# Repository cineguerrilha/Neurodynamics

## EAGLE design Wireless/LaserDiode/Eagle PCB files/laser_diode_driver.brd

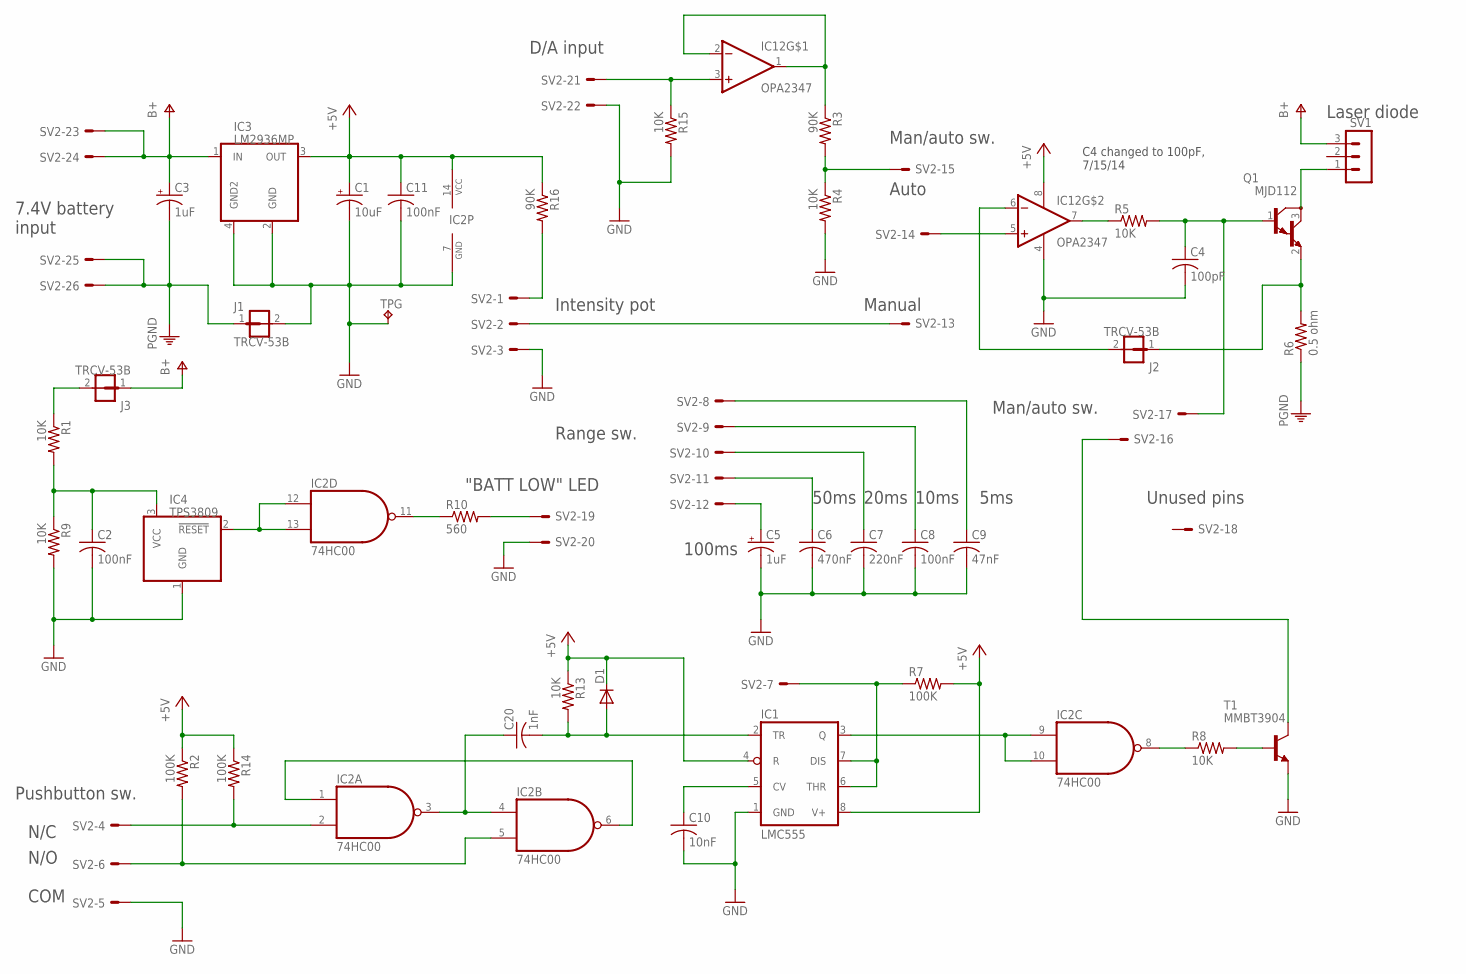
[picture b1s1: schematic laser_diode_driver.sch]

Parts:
C1: 10uF; SMC_B
C2, C8, C11: 100nF; C0805
C3, C5: 1uF; SMC_B
C4: 100pF; C0805
C6: 470nF; C0805
C7: 220nF; C0805
C9: 47nF; C0805
C10: 10nF; C0805
C20: 1nF; C0805
D1: DIODE-SOD123; SOD123
IC1: LMC555; SO08
IC2: 74HC00; SO14
IC3: LM2936MP; SOT223
IC4: TPS3809; SOT23
IC12: OPA2347; SO08
J1, J2, J3: TRCV-53B; JUMPER-TRACE-CONVERT-53-VER2
Q1: MJD112; TO252
R1, R4, R5, R8, R9, R13, R15: 10K; R0805
R2, R7, R14: 100K; R0805
R3, R16: 90K; R0805
R6: 0.5 ohm; R2512
R10: 560; R0805
SV1: MA03-1
SV2: ML26LE; ML26L
T1: MMBT3904; SOT23-BEC
TPG: TP-040-100; P1-040-100

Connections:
+5V: C1.+, C11.1, D1.C, IC1.4 (R), IC1.8 (V+), IC2.14 (VCC), IC3.3 (OUT), IC12.8 (PWR+), R2.1, R7.2, R13.1, R14.1, R16.1
B+: C3.+, IC3.1 (IN), J3.1, SV1.3, SV2.23, SV2.24
GND: C1.-, C2.2, C4.2, C5.-, C6.2, C7.2, C8.2, C9.2, C10.2, C11.2, IC1.1 (GND), IC2.7 (GND), IC3.2 (GND), IC3.4 (GND2), IC4.1 (GND), IC12.4 (PWR-), J1.2, R4.2, R9.2, R15.2, SV2.3, SV2.5, SV2.20, SV2.22, T1.E, TPG.P$1
unnamed: C20.1, IC2.3 (O), IC2.4 (I0)
unnamed: IC12.5 (+IN), SV2.14
unnamed: IC2.1 (I0), IC2.6 (O)
unnamed: IC2.2 (I1), R14.2, SV2.4
unnamed: IC2.5 (I1), R2.2, SV2.6
unnamed: C20.2, D1.A, IC1.2 (TR), R13.2
unnamed: C5.+, SV2.12
unnamed: IC12.7 (OUT), R5.1
unnamed: C4.1, Q1.1 (B), R5.2, SV2.17
unnamed: R16.2, SV2.1
unnamed: IC12.3 (+IN), R15.1, SV2.21
unnamed: IC12.1 (OUT), IC12.2 (-IN), R3.1
unnamed: R3.2, R4.1, SV2.15
unnamed: SV2.2, SV2.13
unnamed: Q1.3 (C), SV1.1
unnamed: IC12.6 (-IN), J2.2
unnamed: C6.1, SV2.11
unnamed: C7.1, SV2.10
unnamed: C8.1, SV2.9
unnamed: C9.1, SV2.8
unnamed: IC1.6 (THR), IC1.7 (DIS), R7.1, SV2.7
unnamed: C10.1, IC1.5 (CV)
unnamed: IC1.3 (Q), IC2.9 (I0), IC2.10 (I1)
unnamed: IC2.8 (O), R8.1
unnamed: R8.2, T1.B
unnamed: SV2.16, T1.C
unnamed: C2.1, IC4.3 (VCC), R1.2, R9.1
unnamed: J2.1, Q1.2 (E), R6.2
unnamed: IC2.12 (I0), IC2.13 (I1), IC4.2 (!RESET)
unnamed: IC2.11 (O), R10.1
unnamed: R10.2, SV2.19
unnamed: J3.2, R1.1
PGND: C3.-, J1.1, R6.1, SV2.25, SV2.26

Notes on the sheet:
Intensity pot
Man/auto sw.
Pushbutton sw.
D/A input
N/C
N/O
"BATT LOW" LED
Range sw.
Auto
Manual
7.4V battery input
Unused pins
Laser diode
COM
5ms
10ms
20ms
50ms
100ms
C4 changed to 100pF, 7/15/14

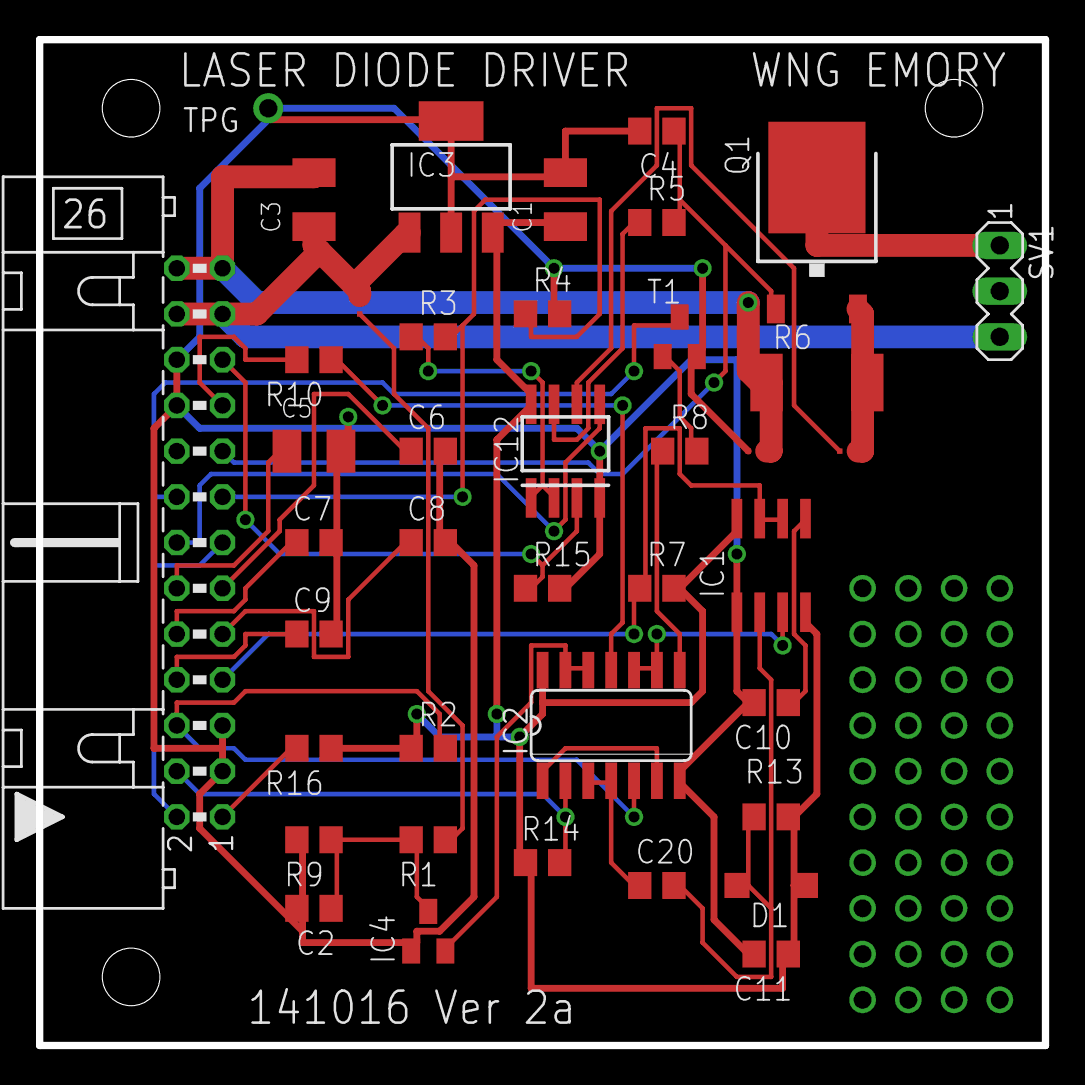
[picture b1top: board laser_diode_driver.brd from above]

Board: 4 copper layers, 55.9 x 55.9 mm, 40 parts (0 on the bottom side), 36 nets.

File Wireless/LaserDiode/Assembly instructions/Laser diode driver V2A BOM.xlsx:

Quan. | Value | Eagle Device | Part names | Digikey p/n | Notes
PC Board Parts - vendor: Digikey (www.digikey.com)
1.0 | 0.5 ohm | R-US_R2512 | R6 | CSRN2512FKR500CT-ND
1.0 | 560 | R-US_R0805 | R10 | 311-560CRCT-ND
7.0 | 10K | R-US_R0805 | R1 R4 R5 R8 R9 R13 R15 | 311-10.0KCRCT-ND
2.0 | 90.9K | R-US_R0805 | R3 R16 | 311-90.9KCRCT-ND
3.0 | 100K | R-US_R0805 | R2 R7 R14 | 311-100KCRCT-ND
1.0 | 100pF | C-USC0805 | C4 | 399-7981-1-ND
1.0 | 1nF | C-USC0805 | C20 | 399-1147-1-ND
1.0 | 10nF | C-USC0805 | C10 | 399-1158-1-ND
1.0 | 47nF | C-USC0805 | C9 | 399-1166-1-ND
3.0 | 100nF | C-USC0805 | C2 C8 C11 | 399-1170-1-ND
1.0 | 220nF | C-USC0805 | C7 | 399-3491-1-ND
1.0 | 470nF | C-USC0805 | C6 | 399-8098-1-ND
2.0 | 1uF | CPOL-USSMCB | C3 C5 | 399-3680-1-ND | polarized
1.0 | 10uF | CPOL-USSMCB | C1 | 399-8269-1-ND | polarized
1.0 | LM2936MP | LM2936MP | IC3 | 296-37374-1-ND | voltage regulator
1.0 | LMC555 | LM555D | IC1 | LMC555CMX/NOPBCT-ND | timer
1.0 | MJD112 | MJD112 | Q1 | 497-2462-1-ND | darlington transistor
1.0 | MMBT3904 | MMBT3904LT1 | T1 | MMBT3904LT1GOSCT-ND | NPN transistor
1.0 | 74HC00 | 74ALS00D | IC2 | 568-1379-1-ND | NAND gate
1.0 | OPA2347 | OPA2227-SO8 | IC12 | OPA2347UACT-ND | op amp
1.0 | TP-040-100 | TP-040-100 | TPG | 5001K-nd | test point
1.0 | TPS3809K33 | TPS3809 | IC4 | 296-15644-1-NS | low-battery warning
1.0 |  | DIODE-SOD123 | D1 | 1N4148WTPMSCT-ND | diode
1.0 |  | MA03-1 | SV1 | A19470-ND | 3-pin connector
1.0 |  |  |  | A99614-ND | mate for MA03
3.0 |  |  |  | A99620 | pins for MA03
1.0 |  | ML26LE | SV2 | A97488-ND | 26-pin IDC connector
1.0 |  |  |  | CKC26G | IDC socket for above
1.0 |  |  |  | MC26M-5-ND | 26-cond. ribbon cable
Off-board parts
1.0 |  |  | S1 | CKN1649-ND, CKN1210-ND | pushbutton and cap
1.0 |  |  | S2 | GH5604-ND | range switch
1.0 |  |  | S3 | CKN1034-ND | manual/auto switch
1.0 |  |  | S4 | 450-1523-ND | power switch
1.0 |  |  | J1 | CP-6-ND | charging jack
1.0 |  |  | P1 | CP3-1001-ND | charging plug
1.0 | 10K |  | VR1 | 95A1A-B24-A15L-ND | intensity pot
2.0 |  |  | J2 J3 | ARFX1063 | BNC receptable
1.0 |  |  | LED1 | 67-1147-ND | low-battery LED
2.0 |  |  |  | 708-1412-ND | battery holders
1.0 |  |  |  | HM162-ND | enclosure
Non-Digikey parts |  | Vendor | Part Number | Website | Notes
2.0 | Ultrafire 16340 | Fasttech | 1055500.0 | www.fasttech.com | 3.7V Li-Ion batteries
1.0 | TLP-4000 (01281) | Newegg | 9SIA2EY0ZU2250 | www.newegg.com | charger
1.0 | 12mm module w/ lens | DTR's Lasers |  | https://sites.google.com/site/dtrlpf/home/diode-modules | laser diode
1.0 |  | OshPark | Laser Diode Driver, Ver 2a | www.oshpark.com | printed circuit board
1.0 |  | Thorlabs | F240FC-A | www.thorlabs.com | collimator
1.0 |  | Thorlabs | M83L01 | www.thorlabs.com | fiber optic cable
1.0 |  | custom machined |  |  | collimator adapter
W.N. Goolsby
42360.0

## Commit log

2016-02-14 more stuff w franzon
2018-03-22 Matlab miniscope routines
2018-04-12 New patch clamp scripts
    New epsc/ipsc detection files
    New loading routines
    New AP analysis
2018-06-07 New files for matlab
    For analysis of patch and reading files from the in vivo computer
2018-08-22 More miniscope routines
    New miniscope routines
    CameraLedBlink
    BahavePos
    LoadPreviousRoi
2018-08-22 Coherence in time
2018-09-07 commit 7/9
2018-09-11 Small changes for video analysis
2018-09-12 Coherence by coordinate
2018-10-09 Coherence
2018-10-09 small changes
2018-10-18 minor
2018-10-20 Center and border also calculates coherence center and border
2018-11-09 New patch clamp routines and in vivo analysis tools
2018-11-09 save the masked video
2018-11-10 small changes in the mini detection
2018-11-11 small changes in epm coherence
2018-11-11 EPM analysis corrected
2018-12-19 more small changes
2019-06-20 circular array
2020-08-22 auditory miniscope stuff
2020-12-03 New DLC and place cell routines
2021-01-19 new dlc routines
2021-01-20 run video tracking
2021-01-24 new getSpikes caller
2021-01-25 minor fixes
2021-01-26 spike
